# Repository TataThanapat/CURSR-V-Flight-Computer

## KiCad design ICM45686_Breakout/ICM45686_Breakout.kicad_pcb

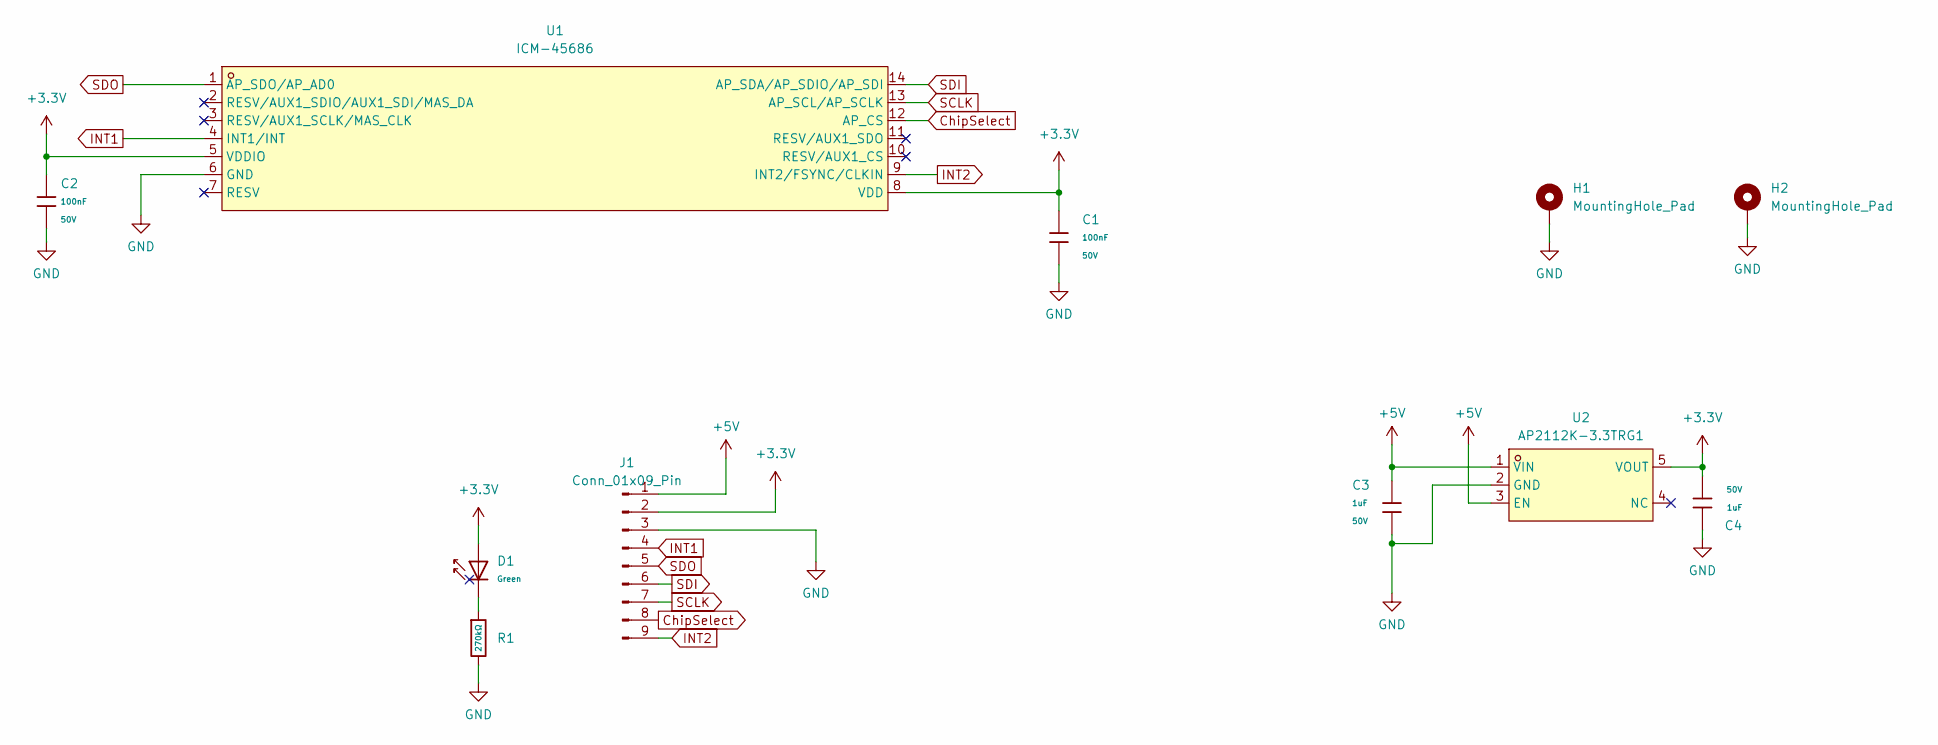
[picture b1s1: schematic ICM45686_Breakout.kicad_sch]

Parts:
C1, C2: 100nF; C_0603; Voltage Rated 50V; Tolerance ±10%; Part CC0603KRX7R9BB104; LCSC C14663
C3, C4: 1uF; C_0805; Voltage Rated 50V; Tolerance ±10%; Part CL21B105KBFNNNE; LCSC C28323
D1: Green; D_0805; Part KT-0805G; LCSC C2297
H1, H2: MountingHole_Pad; MountingHole_2.2mm_M2_ISO7380_Pad
J1: Conn_01x09_Pin; PinHeader_1x09_P2.54mm_Vertical
R1: 270kΩ; R_0603; Overload Voltage (Max) 75V; Tolerance ±1%; Part 0603WAF2703T5E; LCSC C22965
U1: ICM-45686; LGA-14_L3.0-W2.5-P0.50-TL; LCSC Part C22459454
U2: AP2112K-3.3TRG1; SOT-25-5_L2.9-W1.6-P0.95-LS2.8-BL; LCSC Part C51118

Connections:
+3.3V: C1.1, C2.1, C4.2, D1.2, J1.2, U1.5 (VDDIO), U1.8 (VDD), U2.5 (VOUT)
+5V: C3.1, J1.1, U2.1 (VIN), U2.3 (EN)
ChipSelect: J1.8, U1.12 (AP_CS)
GND: C1.2, C2.2, C3.2, C4.1, H1.1, H2.1, J1.3, R1.2, U1.6 (GND), U2.2 (GND)
INT1: J1.4, U1.4 (INT1/INT)
INT2: J1.9, U1.9 (INT2/FSYNC/CLKIN)
unnamed: D1.1, R1.1
SCLK: J1.7, U1.13 (AP_SCL/AP_SCLK)
SDI: J1.6, U1.14 (AP_SDA/AP_SDIO/AP_SDI)
SDO: J1.5, U1.1 (AP_SDO/AP_AD0)

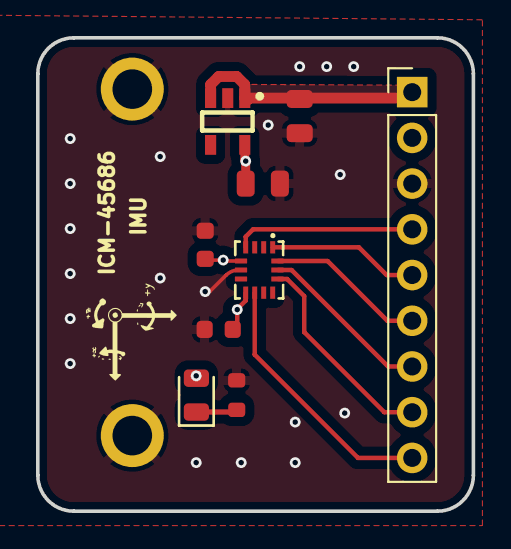
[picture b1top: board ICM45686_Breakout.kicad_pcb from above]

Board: 4 copper layers, 24.2 x 26.3 mm, 11 parts (0 on the bottom side), 10 nets.

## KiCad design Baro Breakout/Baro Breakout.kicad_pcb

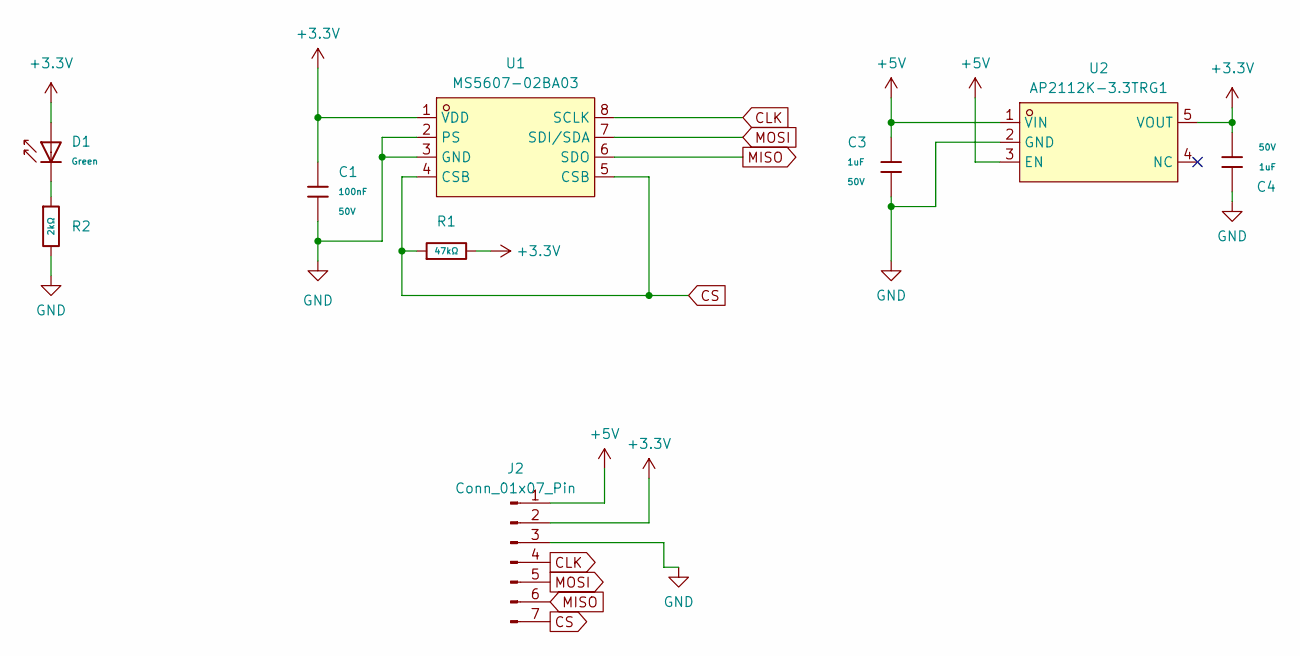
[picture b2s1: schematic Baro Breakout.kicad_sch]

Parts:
C1: 100nF; C_0603; Voltage Rated 50V; Tolerance ±10%; Part CC0603KRX7R9BB104; LCSC C14663
C3, C4: 1uF; C_0805; Voltage Rated 50V; Tolerance ±10%; Part CL21B105KBFNNNE; LCSC C28323
D1: Green; D_0805; Part KT-0805G; LCSC C2297
J2: Conn_01x07_Pin; PinHeader_1x07_P2.54mm_Vertical
R1: 47kΩ; R_0603; Overload Voltage (Max) 75V; Tolerance ±1%; Part 0603WAF4702T5E; LCSC C25819
R2: 2kΩ; R_0402; Overload Voltage (Max) 50V; Tolerance ±1%; Part 0402WGF2001TCE; LCSC C4109
U1: MS5607-02BA03; SENSOR-SMD_MS560702BA03-50; LCSC Part C9900023641
U2: AP2112K-3.3TRG1; SOT-25-5_L2.9-W1.6-P0.95-LS2.8-BL; LCSC Part C51118

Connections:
+3.3V: C1.1, C4.2, D1.2, J2.2, R1.2, U1.1 (VDD), U2.5 (VOUT)
+5V: C3.1, J2.1, U2.1 (VIN), U2.3 (EN)
CLK: J2.4, U1.8 (SCLK)
CS: J2.7, R1.1, U1.4 (CSB), U1.5 (CSB)
GND: C1.2, C3.2, C4.1, J2.3, R2.2, U1.2 (PS), U1.3 (GND), U2.2 (GND)
MISO: J2.6, U1.6 (SDO)
MOSI: J2.5, U1.7 (SDI/SDA)
unnamed: D1.1, R2.1

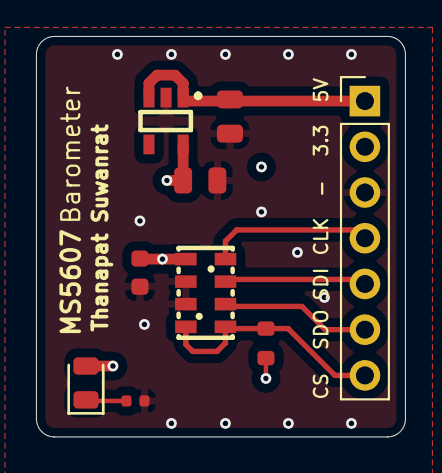
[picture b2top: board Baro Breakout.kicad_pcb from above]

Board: 4 copper layers, 20.5 x 22.2 mm, 9 parts (0 on the bottom side), 8 nets.

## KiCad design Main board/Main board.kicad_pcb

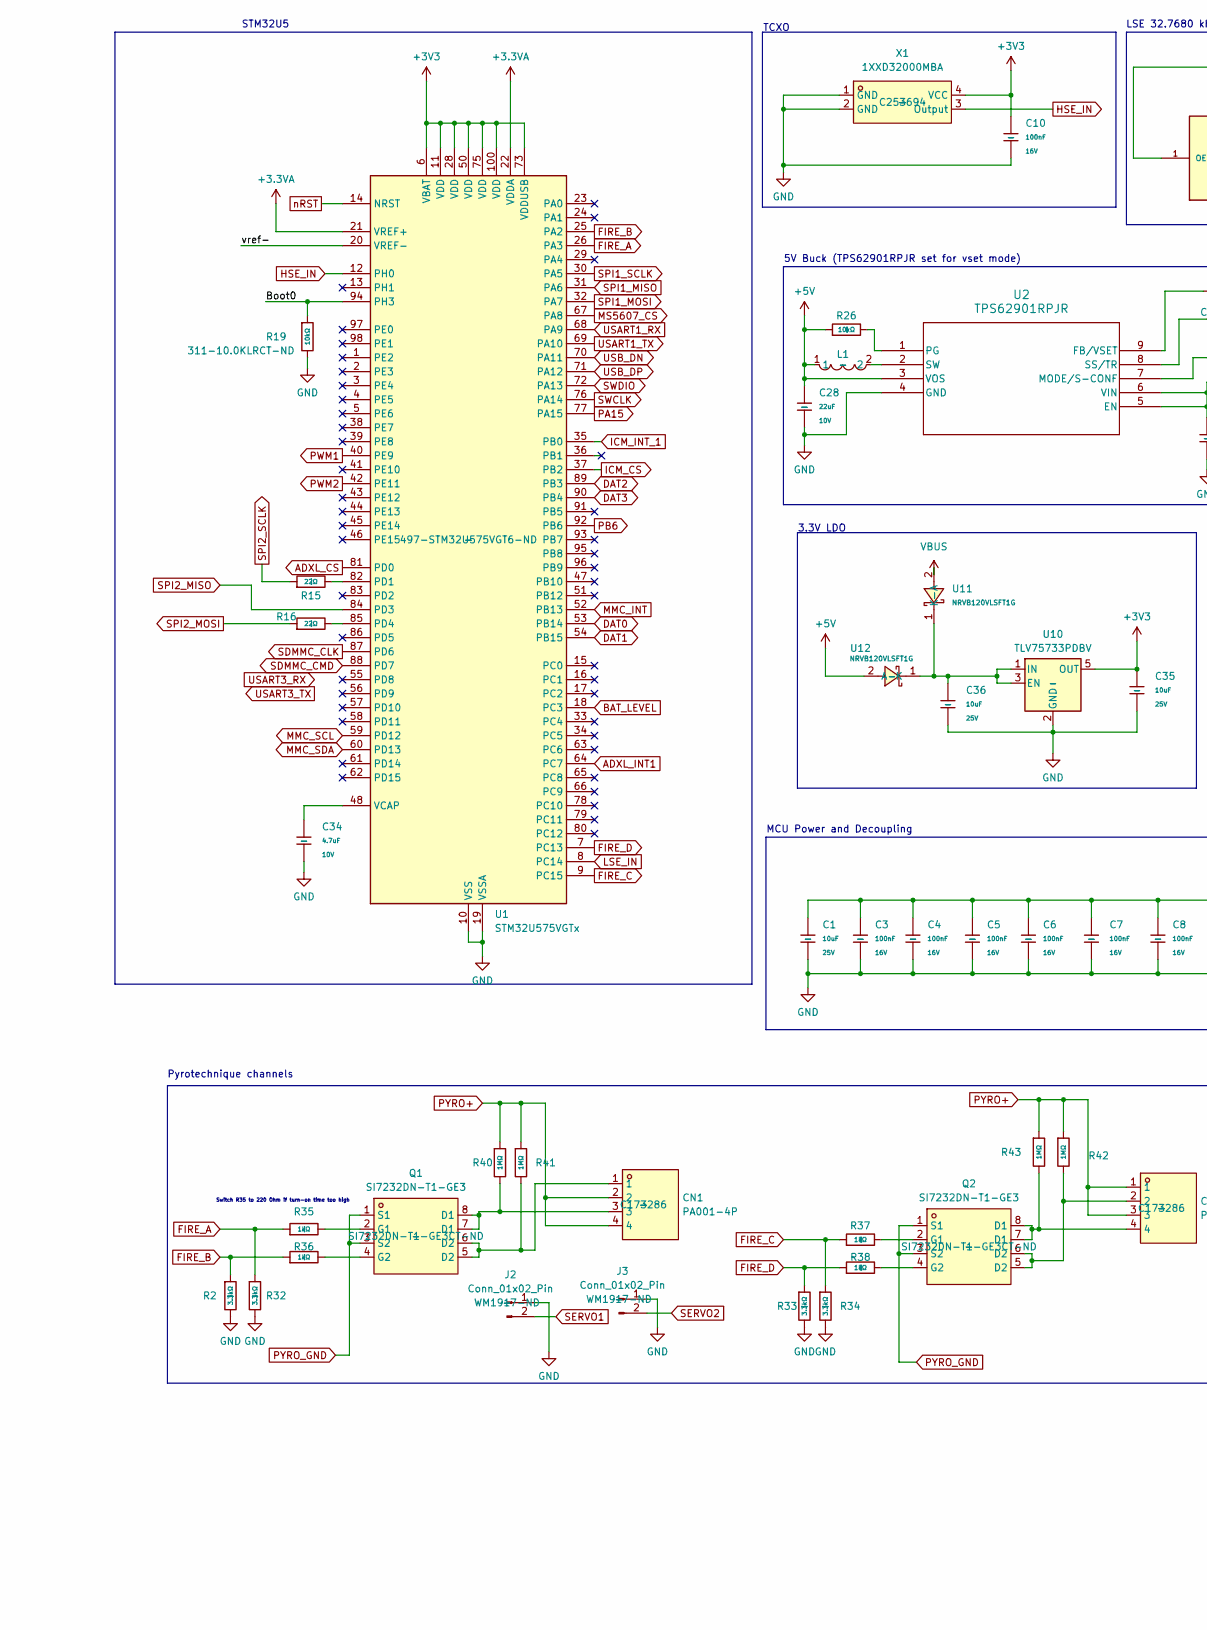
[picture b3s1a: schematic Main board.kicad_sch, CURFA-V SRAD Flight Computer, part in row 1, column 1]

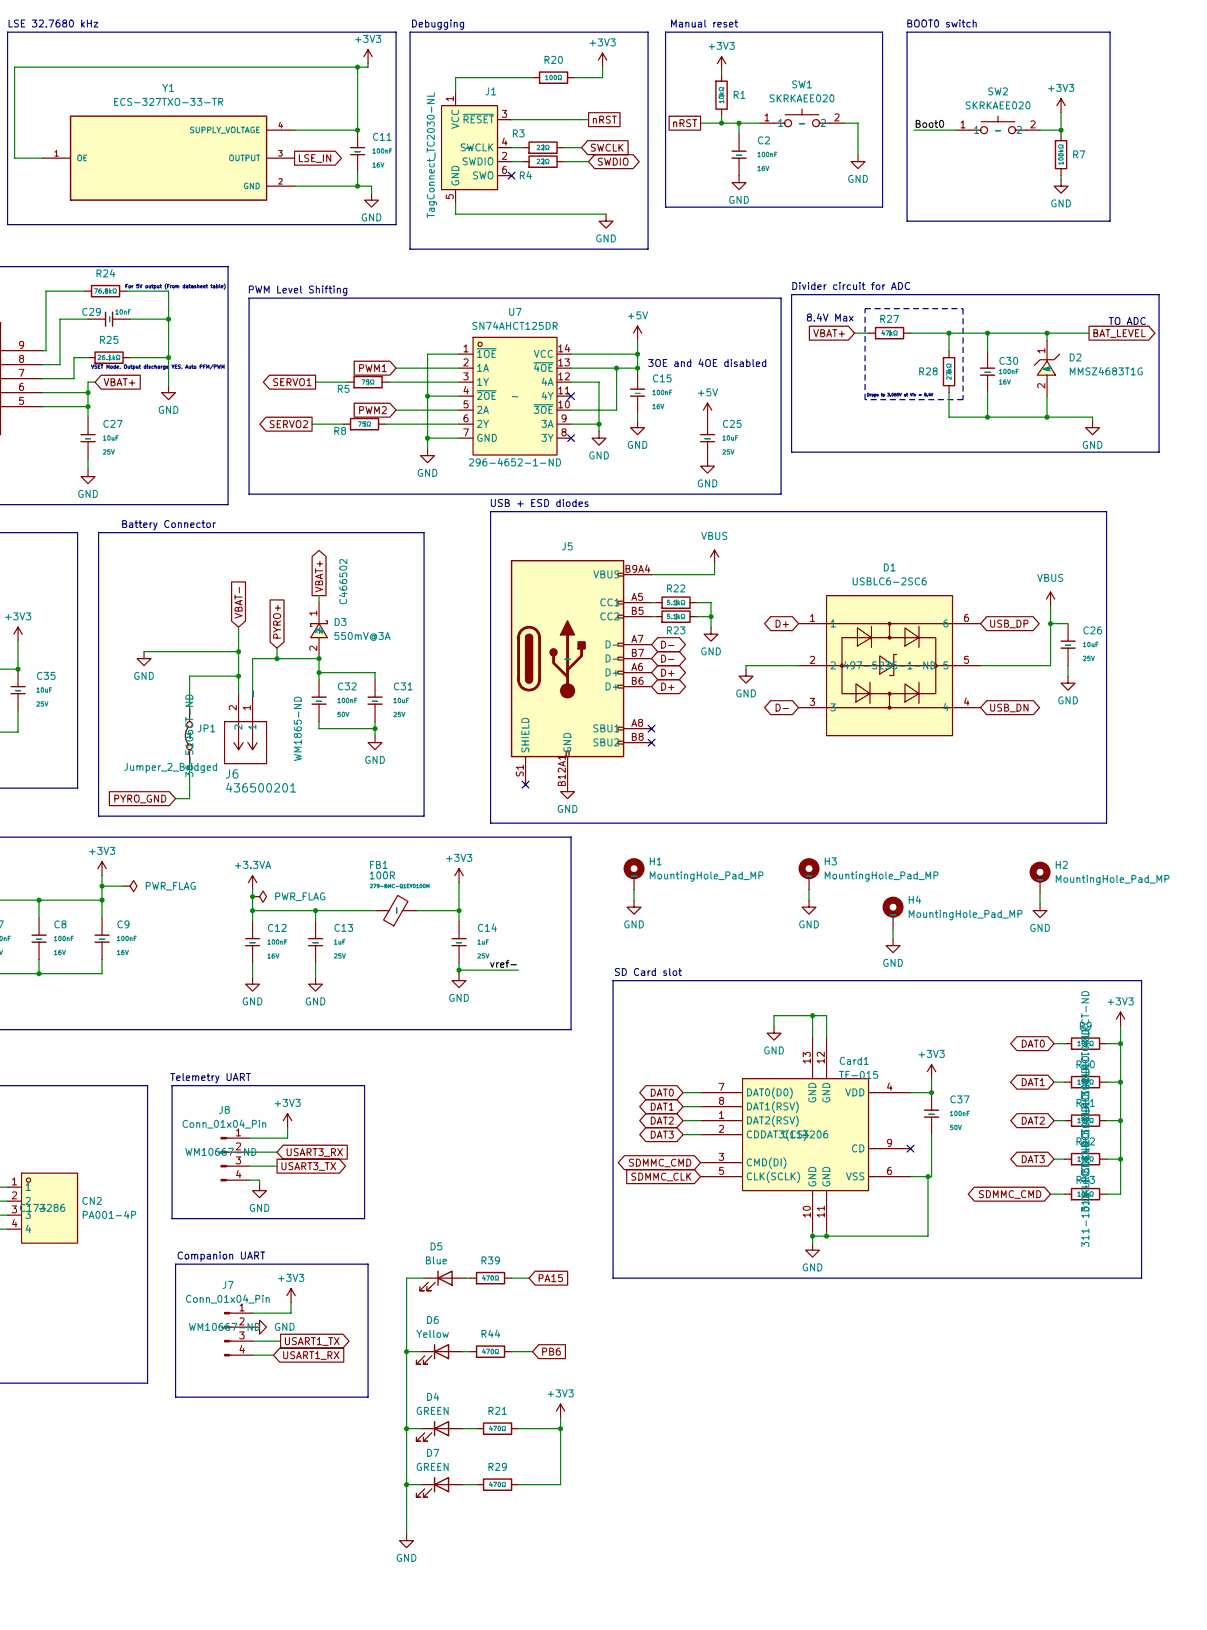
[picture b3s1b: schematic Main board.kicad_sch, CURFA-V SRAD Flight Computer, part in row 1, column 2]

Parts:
C1, C25, C26, C35, C36: 10uF; C_0603; Voltage Rated 25V; Tolerance ±20%; Part CL05A106MQ5NUNC; LCSC C96446
C2, C3, C4, C5, C6, C7, C8, C9, C10, C11, C12, C15, C30: 100nF; C_0402; Voltage Rated 16V; Tolerance ±10%; Part CL05B104KO5NNNC; LCSC C1525
C13, C14: 1uF; C_0402; Voltage Rated 25V; Tolerance ±10%; Part CL05A105KA5NQNC; LCSC C52923
C27, C31: 10uF; C_0603; Voltage Rated 25V; Tolerance ±20%; Part CL10A106MA8NRNC; LCSC C96446
C28: 22uF; C_0805; Voltage Rated 10V; Tolerance ±20%; Part CL10A226MQ8NRNC; LCSC C380338
C29: 10nF; C_0402; Voltage Rated 50V; Tolerance ±10%; Part CL05B103KB5NNNC; LCSC C15195
C32, C37: 100nF; C_0603; Voltage Rated 50V; Tolerance ±10%; Part CC0603KRX7R9BB104; LCSC C14663
C34: 4.7uF; C_0805; Voltage Rated 10V; Tolerance ±20%; Part CL05A475MP5NRNC; LCSC C76639
CN1, CN2: PA001-4P; CONN-TH_4P-P5.08_PA001-4P; LCSC Part C173286
Card1: TF-015; TF-SMD_TF-015; LCSC Part C113206
D1: USBLC6-2SC6; SOT-23-6_L2.9-W1.6-P0.95-LS2.8-BL; LCSC Part C7519
D2: MMSZ4683T1G; SOD-123_L2.8-W1.8-LS3.7-RD; LCSC Part C235985
D3: 550mV@3A; SMA_L4.4-W2.6-LS5.0-RD; LCSC Part C466502
D4, D7: GREEN; WL-SMCW_0603
D5: Blue; WL-SMCW_0603
D6: Yellow; WL-SMCW_0603
FB1: 100R; C_0402_1005Metric_Pad0.74x0.62mm_HandSolder; Part 279-BMC-Q1EY0100M
H1, H2, H3, H4: MountingHole_Pad_MP; MountingHole_3.2mm_M3_DIN965_Pad_TopBottom
J1: TagConnect_TC2030-NL; Tag-Connect_TC2030-IDC-NL_2x03_P1.27mm_Vertical
J2, J3: Conn_01x02_Pin; Molex_Micro-Fit_3.0_43650-0215_1x02_P3.00mm_Vertical; Digikey Part No. WM1917-ND
J5: Connector, USB-TYPE-C-16P; TYPE-C-SMD_HX-TYPE-C-16PIN; LCSC C2927039
J6: 436500201; AMASS_XT30UPB-F_1x02_P5.0mm_Vertical; Digikey Part No. WM1865-ND
J7: Conn_01x04_Pin; CONN_SD-43045-010_04_MOL; Digikey Part No. WM10667-ND
J8: Conn_01x04_Pin; PinHeader_1x04_P2.54mm_Vertical; Digikey Part No. WM10667-ND
JP1: Jumper_2_Bridged; D_0805_2012Metric; Digikey Part No. 36-5106CT-ND
L1: CKCS4018-1UH/N; IND-SMD_L4.0-W4.0; LCSC Part C354578
Q1, Q2: SI7232DN-T1-GE3; POWER-1212-8_L3.3-W3.3-P0.66-LS3.3-BL; LCSC Part C144854
R1, R9, R10, R11, R12, R13, R19: 10kΩ; R_0402; Overload Voltage (Max) 50V; Tolerance ±1%; Part 0402WGF1002TCE; LCSC C25744 (OUT OF STOCK)
R2, R32, R33, R34: 3.3kΩ; R_0402; Overload Voltage (Max) 50V; Tolerance ±1%; Part 0402WGF3301TCE; LCSC C25890
R3, R4, R15, R16: 22Ω; R_0402; Overload Voltage (Max) 50V; Tolerance ±1%; Part 0402WGF220JTCE; LCSC C25092
R5, R8: 75Ω; R_0402; Overload Voltage (Max) 50V; Tolerance ±1%; Part 0402WGF750JTCE; LCSC C25133
R7: 100kΩ; R_0402; Overload Voltage (Max) 50V; Tolerance ±1%; Part 0402WGF1003TCE; LCSC C25741 (OUT OF STOCK)
R20: 100Ω; R_0402; Overload Voltage (Max) 50V; Tolerance ±1%; Part 0402WGF1000TCE; LCSC C25076
R21, R29, R39, R44: 470Ω; R_0402; Overload Voltage (Max) 50V; Tolerance ±1%; Part 0402WGF4700TCE; LCSC C25117
R22, R23: 5.1kΩ; R_0402; Overload Voltage (Max) 50V; Tolerance ±1%; Part 0402WGF5101TCE; LCSC C25905
R24: 76.8kΩ; R_0603; Overload Voltage (Max) 75V; Tolerance ±1%; Part ERJ-P03F7682V; Digikey Part No. 311-76.8KHRCT-ND
R25: 26.1kΩ; R_0603; Overload Voltage (Max) 75V; Tolerance ±1%; Part ERJ-S03F2612V; Digikey Part No. 311-26.1KHRCT-ND
R26: 10kΩ; R_0603; Overload Voltage (Max) 75V; Tolerance ±1%; Part 0603WAF1002T5E; LCSC C25804
R27: 47kΩ; R_0402; Overload Voltage (Max) 50V; Tolerance ±1%; Part 0402WGF4702TCE; LCSC C25792
R28: 27kΩ; R_0402; Overload Voltage (Max) 50V; Tolerance ±1%; Part 0402WGF2702TCE; LCSC C25771
R35, R36, R37, R38: 1kΩ; R_0402; Overload Voltage (Max) 50V; Tolerance ±1%; Part 0402WGF1001TCE; LCSC C11702
R40, R41, R42, R43: 1MΩ; R_0805; Overload Voltage (Max) 150V; Tolerance ±1%; Part 0805W8F1004T5E; LCSC C17514
SW1, SW2: SKRKAEE020; SW-SMD_L3.9-W3.0-P4.45; LCSC Part C115357
U1: STM32U575VGTx; LQFP-100_14x14mm_P0.5mm; Digikey Part No. 497-STM32U575VGT6-ND
U2: TPS62901RPJR; QFN_902RPJR_TEX; Digikey Part No. 296-TPS62901RPJRCT-ND
U7: SN74AHCT125DR; SOIC-14_L8.7-W3.9-P1.27-LS6.0-BL; LCSC Part C155176
U10: TLV75733PDBV; SOT-23-5; Digikey Part No. 296-50414-1-ND
U11, U12: NRVB120VLSFT1G; SOD-123_L2.7-W1.6-LS3.7-RD-1; LCSC Part C604264
X1: 1XXD32000MBA; OSC-SMD_4P-L2.0-W1.6-BL_1XXD; LCSC Part C253694
Y1: ECS-327TXO-33-TR; OSC_ECS-327TXO-33-TR; PARTREV Rev.2019

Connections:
+3.3VA: C12.1, C13.1, FB1.1, U1.21 (VREF+), U1.22 (VDDA)
+3V3: C1.1, C3.1, C4.1, C5.1, C6.1, C7.1, C8.1, C9.1, C10.1, C11.1, C14.1, C35.1, C37.1, Card1.4 (VDD), FB1.2, J7.1, J8.1, R1.1, R7.1, R9.2, R10.2, R11.2, R12.2, R13.2, R20.2, R21.2, R29.2, SW2.2, U1.6 (VBAT), U1.11 (VDD), U1.28 (VDD), U1.50 (VDD), U1.73 (VDDUSB), U1.75 (VDD), U1.100 (VDD), U10.5 (OUT), X1.4 (VCC), Y1.1 (OE), Y1.4 (SUPPLY_VOLTAGE); also elsewhere on the board
+5V: C15.1, C25.1, C28.1, L1.1, R26.1, U2.3 (VOS), U7.10 (~3OE), U7.13 (~4OE), U7.14 (VCC), U12.2 (A)
/Boot0: R19.1, SW2.1, U1.94 (PH3)
ADXL_CS: U1.81 (PD0); also elsewhere on the board
ADXL_INT1: U1.64 (PC7); also elsewhere on the board
BAT_LEVEL: C30.1, D2.1 (C), R27.2, R28.1, U1.18 (PC3)
D+: D1.1, J5.A6 (D+), J5.B6 (D+)
D-: D1.3, J5.A7 (D-), J5.B7 (D-)
DAT0: Card1.7 (DAT0(D0)), R9.1, U1.53 (PB14)
DAT1: Card1.8 (DAT1(RSV)), R10.1, U1.54 (PB15)
DAT2: Card1.1 (DAT2(RSV)), R11.1, U1.89 (PB3)
DAT3: Card1.2 (CDDAT3(CS)), R12.1, U1.90 (PB4)
FIRE_A: R32.1, R35.1, U1.26 (PA3)
FIRE_B: R2.1, R36.1, U1.25 (PA2)
FIRE_C: R34.1, R37.1, U1.9 (PC15)
FIRE_D: R33.1, R38.1, U1.7 (PC13)
HSE_IN: U1.12 (PH0), X1.3 (Output)
ICM_CS: U1.37 (PB2); also elsewhere on the board
ICM_INT_1: U1.35 (PB0); also elsewhere on the board
LSE_IN: U1.8 (PC14), Y1.3 (OUTPUT)
MMC_INT: U1.52 (PB13); also elsewhere on the board
MMC_SCL: U1.59 (PD12); also elsewhere on the board
MMC_SDA: U1.60 (PD13); also elsewhere on the board
MS5607_CS: U1.67 (PA8); also elsewhere on the board
unnamed: CN1.1, Q1.5 (D2), Q1.6 (D2), R41.2
unnamed: CN1.3, Q1.7 (D1), Q1.8 (D1), R40.2
unnamed: CN2.2, Q2.5 (D2), Q2.6 (D2), R42.2
unnamed: CN2.4, Q2.7 (D1), Q2.8 (D1), R43.2
unnamed: D4.2 (A), R21.1
unnamed: D5.2 (A), R39.1
unnamed: D6.2 (A), R44.1
unnamed: D7.2 (A), R29.1
unnamed: J1.4 (SWCLK), R3.1
unnamed: J1.2 (SWDIO), R4.1
unnamed: J1.1 (VCC), R20.1
unnamed: J5.A5 (CC1), R22.1
unnamed: J5.B5 (CC2), R23.1
unnamed: Q1.2 (G1), R35.2
unnamed: Q1.4 (G2), R36.2
unnamed: Q2.2 (G1), R37.2
unnamed: Q2.4 (G2), R38.2
unnamed: R15.2, U1.82 (PD1)
unnamed: R16.2, U1.85 (PD4)
unnamed: C34.1, U1.48 (VCAP)
unnamed: R24.2, U2.9 (FB/VSET)
unnamed: R25.1, U2.7 (MODE/S-CONF)
unnamed: R26.2, U2.1 (PG)
unnamed: C29.1, U2.8 (SS/TR)
unnamed: L1.2, U2.2 (SW)
unnamed: R5.2, U7.3 (1Y)
unnamed: R8.2, U7.6 (2Y)
unnamed: C36.1, U10.1 (IN), U10.3 (EN), U11.1 (K), U12.1 (K)
PA15: R39.2, U1.77 (PA15)
PB6: R44.2, U1.92 (PB6)
PWM1: U1.40 (PE9), U7.2 (1A)
PWM2: U1.42 (PE11), U7.5 (2A)
PYRO+: C31.1, C32.1, CN1.2, CN1.4, CN2.1, CN2.3, D3.2, J6.1, R40.1, R41.1, R42.1, R43.1
PYRO_GND: JP1.1 (A), Q1.1 (S1), Q1.3 (S2), Q2.1 (S1), Q2.3 (S2)
SDMMC_CLK: Card1.5 (CLK(SCLK)), U1.87 (PD6)
SDMMC_CMD: Card1.3 (CMD(DI)), R13.1, U1.88 (PD7)
SERVO1: J2.2, R5.1
SERVO2: J3.2, R8.1
SPI1_MISO: U1.31 (PA6); also elsewhere on the board
SPI1_MOSI: U1.32 (PA7); also elsewhere on the board
SPI1_SCLK: U1.30 (PA5); also elsewhere on the board
SPI2_MISO: U1.84 (PD3); also elsewhere on the board
SPI2_MOSI: R16.1; also elsewhere on the board
SPI2_SCLK: R15.1; also elsewhere on the board
SWCLK: R3.2, U1.76 (PA14)
SWDIO: R4.2, U1.72 (PA13)
USART1_RX: J7.4, U1.68 (PA9)
USART1_TX: J7.3, U1.69 (PA10)
USB_DN: D1.4, U1.70 (PA11)
USB_DP: D1.6, U1.71 (PA12)
VBAT+: C27.1, D3.1, R27.1, U2.5 (EN), U2.6 (VIN)
VBAT-: C1.2, C2.2, C3.2, C4.2, C5.2, C6.2, C7.2, C8.2, C9.2, C10.2, C11.2, C12.2, C13.2, C14.2, C15.2, C25.2, C26.2, C27.2, C28.2, C29.2, C30.2, C31.2, C32.2, C34.2, C35.2, C36.2, C37.2, Card1.6 (VSS), Card1.10 (GND), Card1.11 (GND), Card1.12 (GND), Card1.13 (GND), D1.2, D2.2 (A), D4.1 (K), D5.1 (K), D6.1 (K), D7.1 (K), H1.1, H2.1, H3.1, H4.1, J1.5 (GND), J2.1, J3.1, J5.A12B1 (GND), J5.B12A1 (GND), J6.2, J7.2, J8.4, JP1.2 (B), R2.2, R7.2, R19.2, R22.2, R23.2, R24.1, R25.2, R28.2, R32.2, R33.2, R34.2, SW1.2, U1.10 (VSS), U1.19 (VSSA), U1.20 (VREF-), U1.27 (VSS), U1.49 (VSS), U1.74 (VSS), U1.99 (VSS), U2.4 (GND), U7.1 (~1OE), U7.4 (~2OE), U7.7 (GND), U7.9 (3A), U7.12 (4A), U10.2 (GND), X1.1 (GND), X1.2 (GND), Y1.2 (GND); also elsewhere on the board
VBUS: C26.1, D1.5, J5.A9B4 (VBUS), J5.B9A4 (VBUS), U11.2 (A)
nRST: C2.1, J1.3 (~RESET), R1.2, SW1.1, U1.14 (NRST)

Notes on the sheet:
Divider circuit for ADC
Debugging
SD Card slot
PWM Level Shifting
Telemetry UART
Manual reset
Companion UART
Battery Connector
STM32U5
Switch R35 to 220 Ohm if turn-on time too high
5V Buck (TPS62901RPJR set for vset mode)
Pyrotechnique channels
TCXO
3.3V LDO
TO ADC
8.4V Max
LSE 32.7680 kHz
3OE and 4OE disabled
USB + ESD diodes
For 5V output (From datasheet table)
Drops to 3.065V at Vin = 8.4V
VSET Mode, Output discharge YES, Auto PFM/PWM
MCU Power and Decoupling
BOOT0 switch

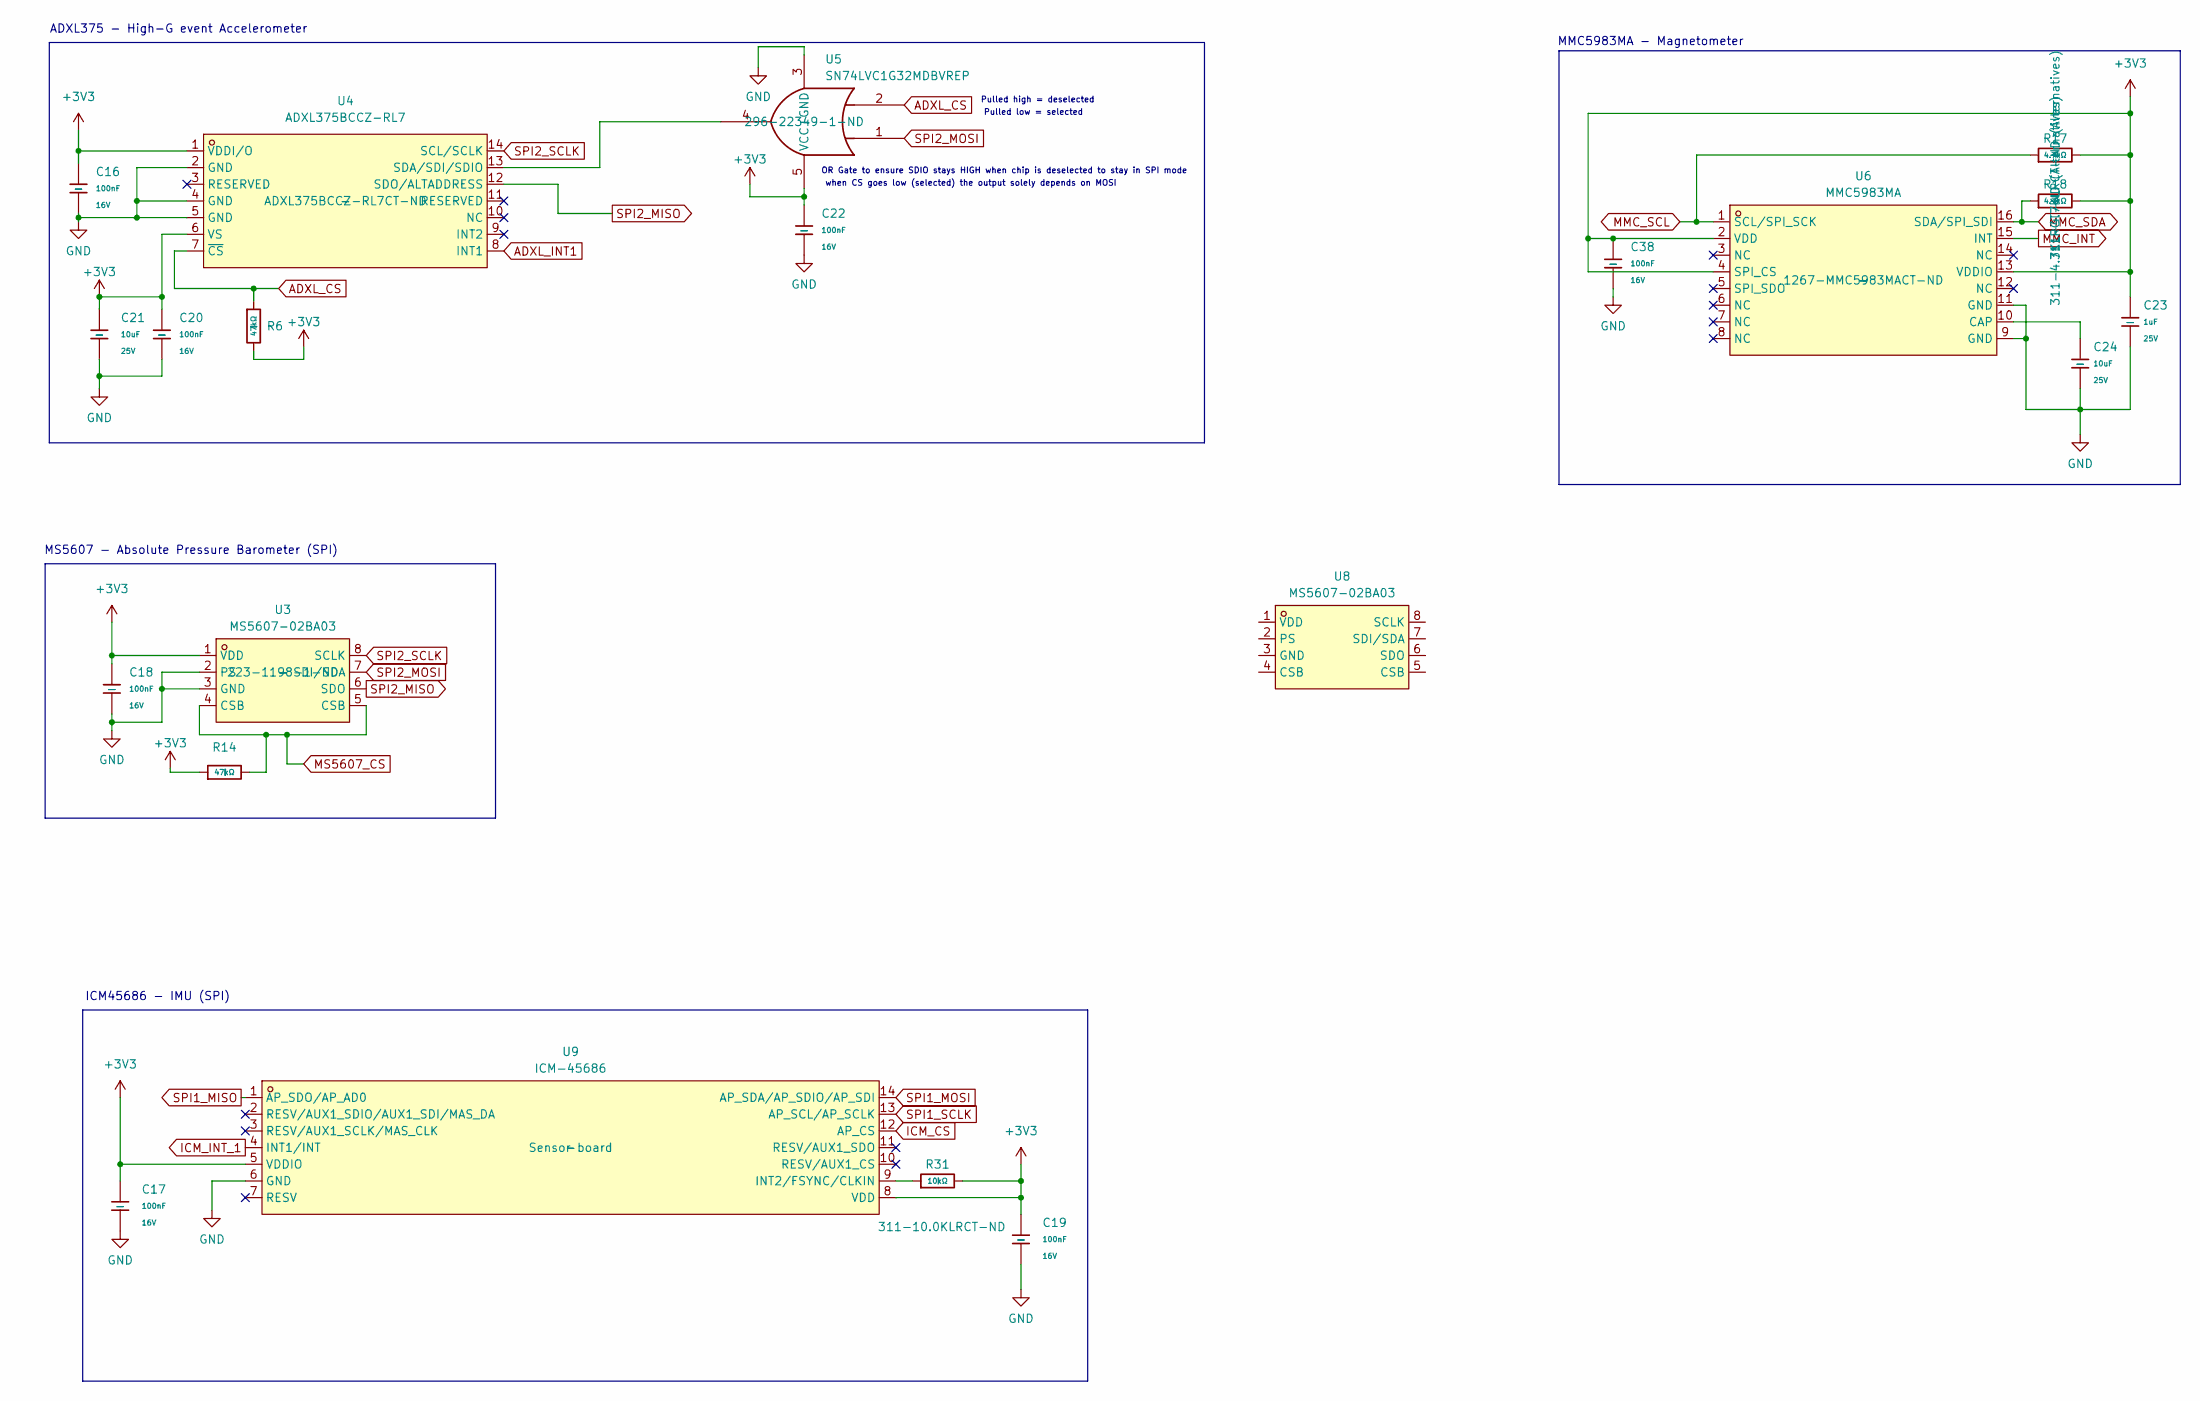
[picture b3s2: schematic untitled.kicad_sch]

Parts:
C16, C17, C18, C19, C20, C22, C38: 100nF; C_0402; Voltage Rated 16V; Tolerance ±10%; Part CL05B104KO5NNNC; LCSC C1525
C21, C24: 10uF; C_0603; Voltage Rated 25V; Tolerance ±20%; Part CL05A106MQ5NUNC; LCSC C96446
C23: 1uF; C_0402; Voltage Rated 25V; Tolerance ±10%; Part CL05A105KA5NQNC; LCSC C52923
R6, R14: 47kΩ; R_0402; Overload Voltage (Max) 50V; Tolerance ±1%; Part 0402WGF4702TCE; LCSC C25792
R17, R18: 4.7kΩ; R_0402; Overload Voltage (Max) 50V; Tolerance ±1%; Part 0402WGF4701TCE; LCSC C25900 (OUT OF STOCK)
R31: 10kΩ; R_0402; Overload Voltage (Max) 50V; Tolerance ±1%; Part 0402WGF1002TCE; LCSC C25744 (OUT OF STOCK)
U3, U8: MS5607-02BA03; SENSOR-SMD_MS560702BA03-50; LCSC Part C9900023641
U4: ADXL375BCCZ-RL7; LGA-14_L5.0-W3.0-P0.80-BL; LCSC Part C481898
U5: SN74LVC1G32MDBVREP; DBV5; Digikey Part No. 296-22349-1-ND
U6: MMC5983MA; LGA-16_L3.0-W3.0-P0.50-BL_SQ; LCSC Part C404329
U9: ICM-45686; LGA-14_L3.0-W2.5-P0.50-TL; LCSC Part C22459454

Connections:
+3V3: C16.1, C17.1, C18.1, C19.1, C20.1, C21.1, C22.1, C23.1, C38.1, R6.2, R14.1, R17.2, R18.2, R31.2, U3.1 (VDD), U4.1 (VDDI/O), U4.6 (VS), U5.5 (VCC), U6.2 (VDD), U6.4 (SPI_CS), U6.13 (VDDIO), U9.5 (VDDIO), U9.8 (VDD); also elsewhere on the board
ADXL_CS: R6.1, U4.7 (~CS), U5.2; also elsewhere on the board
ADXL_INT1: U4.8 (INT1); also elsewhere on the board
ICM_CS: U9.12 (AP_CS); also elsewhere on the board
ICM_INT_1: U9.4 (INT1/INT); also elsewhere on the board
MMC_INT: U6.15 (INT); also elsewhere on the board
MMC_SCL: R17.1, U6.1 (SCL/SPI_SCK); also elsewhere on the board
MMC_SDA: R18.1, U6.16 (SDA/SPI_SDI); also elsewhere on the board
MS5607_CS: R14.2, U3.4 (CSB), U3.5 (CSB); also elsewhere on the board
unnamed: U4.13 (SDA/SDI/SDIO), U5.4
unnamed: C24.1, U6.10 (CAP)
unnamed: R31.1, U9.9 (INT2/FSYNC/CLKIN)
SPI1_MISO: U9.1 (AP_SDO/AP_AD0); also elsewhere on the board
SPI1_MOSI: U9.14 (AP_SDA/AP_SDIO/AP_SDI); also elsewhere on the board
SPI1_SCLK: U9.13 (AP_SCL/AP_SCLK); also elsewhere on the board
SPI2_MISO: U3.6 (SDO), U4.12 (SDO/ALTADDRESS); also elsewhere on the board
SPI2_MOSI: U3.7 (SDI/SDA), U5.1; also elsewhere on the board
SPI2_SCLK: U3.8 (SCLK), U4.14 (SCL/SCLK); also elsewhere on the board
VBAT-: C16.2, C17.2, C18.2, C19.2, C20.2, C21.2, C22.2, C23.2, C24.2, C38.2, U3.2 (PS), U3.3 (GND), U4.2 (GND), U4.4 (GND), U4.5 (GND), U5.3 (GND), U6.9 (GND), U6.11 (GND), U9.6 (GND); also elsewhere on the board

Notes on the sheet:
Pulled low = selected
MS5607 - Absolute Pressure Barometer (SPI)
MMC5983MA - Magnetometer
ICM45686 - IMU (SPI)
Pulled high = deselected
OR Gate to ensure SDIO stays HIGH when chip is deselected to stay in SPI mode
when CS goes low (selected) the output solely depends on MOSI
ADXL375 - High-G event Accelerometer

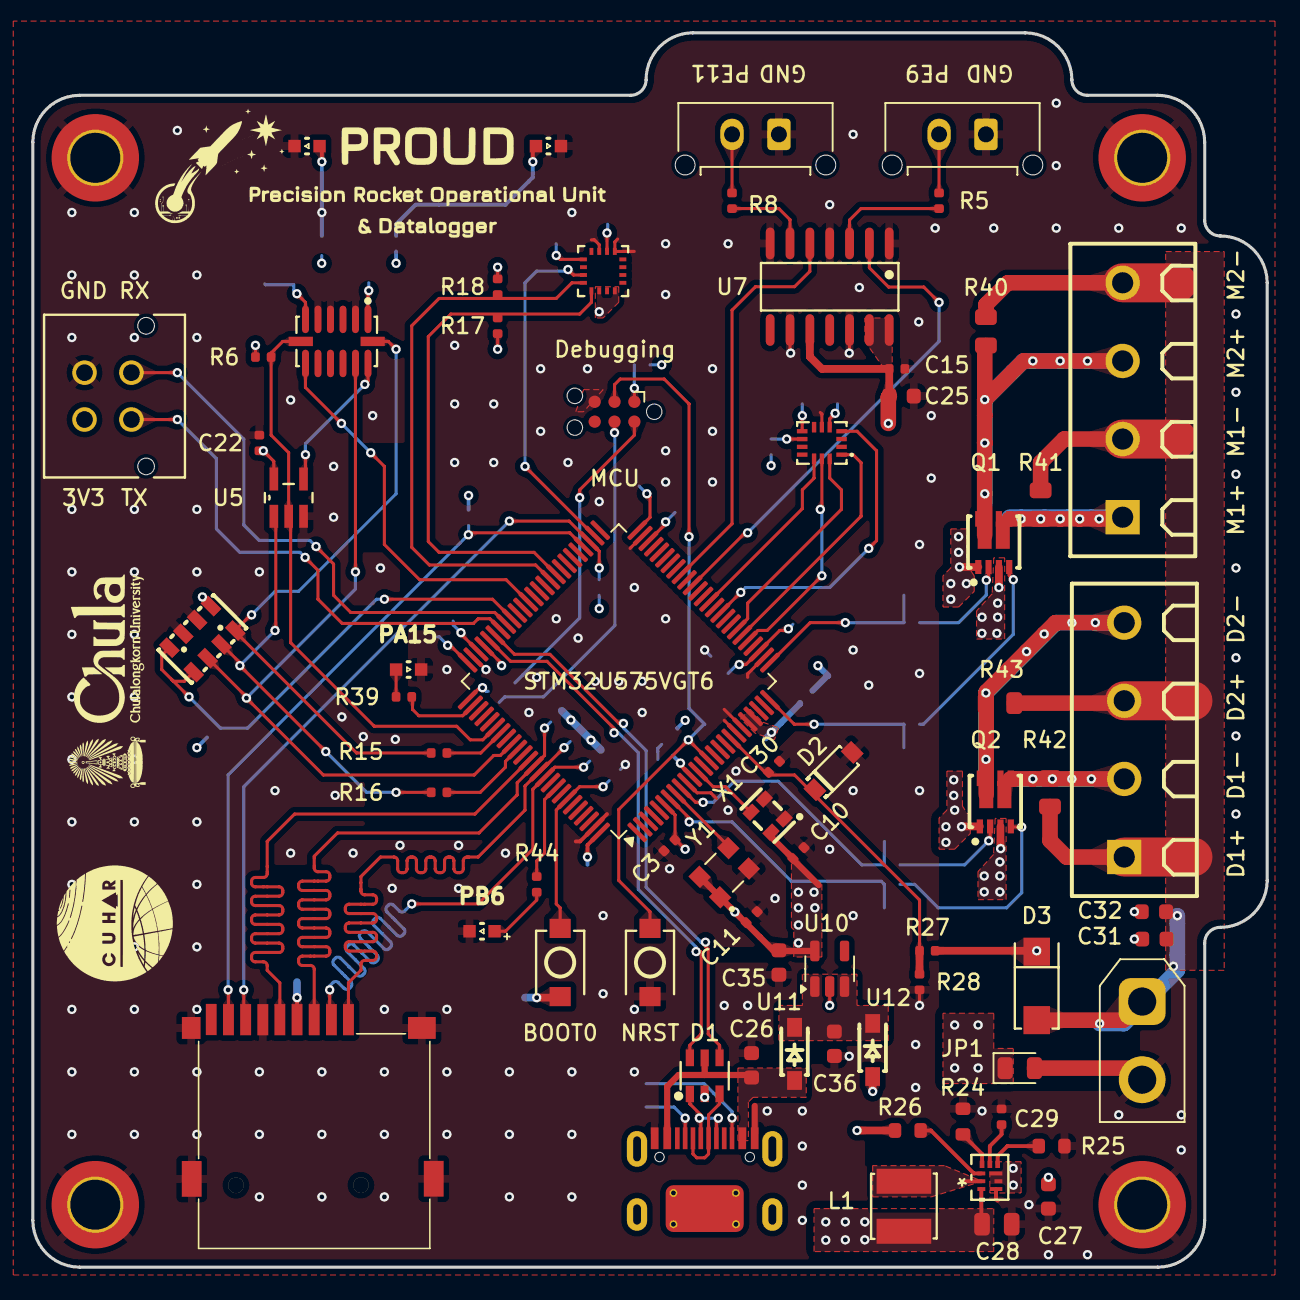
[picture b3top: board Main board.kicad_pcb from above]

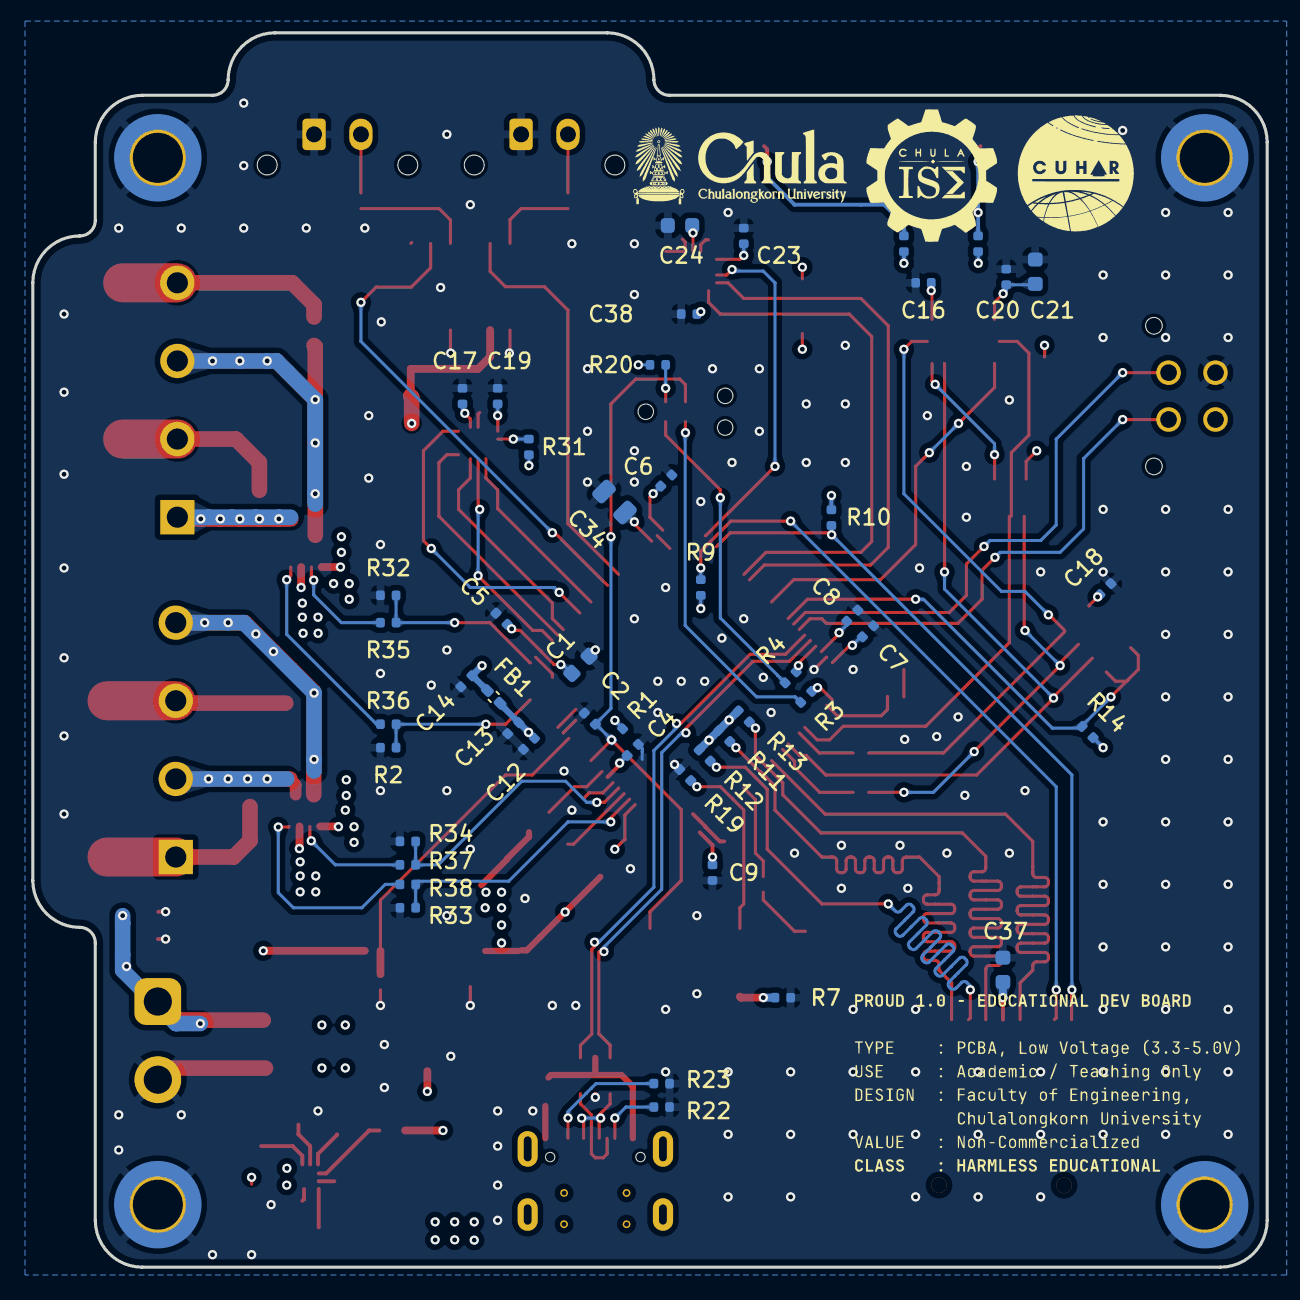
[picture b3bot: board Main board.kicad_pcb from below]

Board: 4 copper layers, 79.0 x 79.0 mm, 120 parts (48 on the bottom side), 82 nets.

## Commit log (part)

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2025-12-10 initial commit
    Initial schematic, layout, and file structures
2025-12-16 Initial Update
    Mainboard schematic update - Added MCU, decoupling, Manual reset, 32MHz TCXO, SD card holder, SWD Tag-connect header, SPI sensors
    Mainboard layout update - Initial SPI routings
    .ioc update - Initial peripheral setups
2026-02-12 Changed to single-board architecture
    SPI Layout #1. Shared bus close to USB D+-, might be bad for layout later.
2026-03-10 Schematics completed + layout
2026-03-16 Layout V1
2026-04-05 Final Layout (Pre-silkscreen)
    - Added 1M resistors in parallel with the igniters for static dissipation
2026-04-06 Minor Adjustment + Silkscreen
2026-06-17 Included IMU project
